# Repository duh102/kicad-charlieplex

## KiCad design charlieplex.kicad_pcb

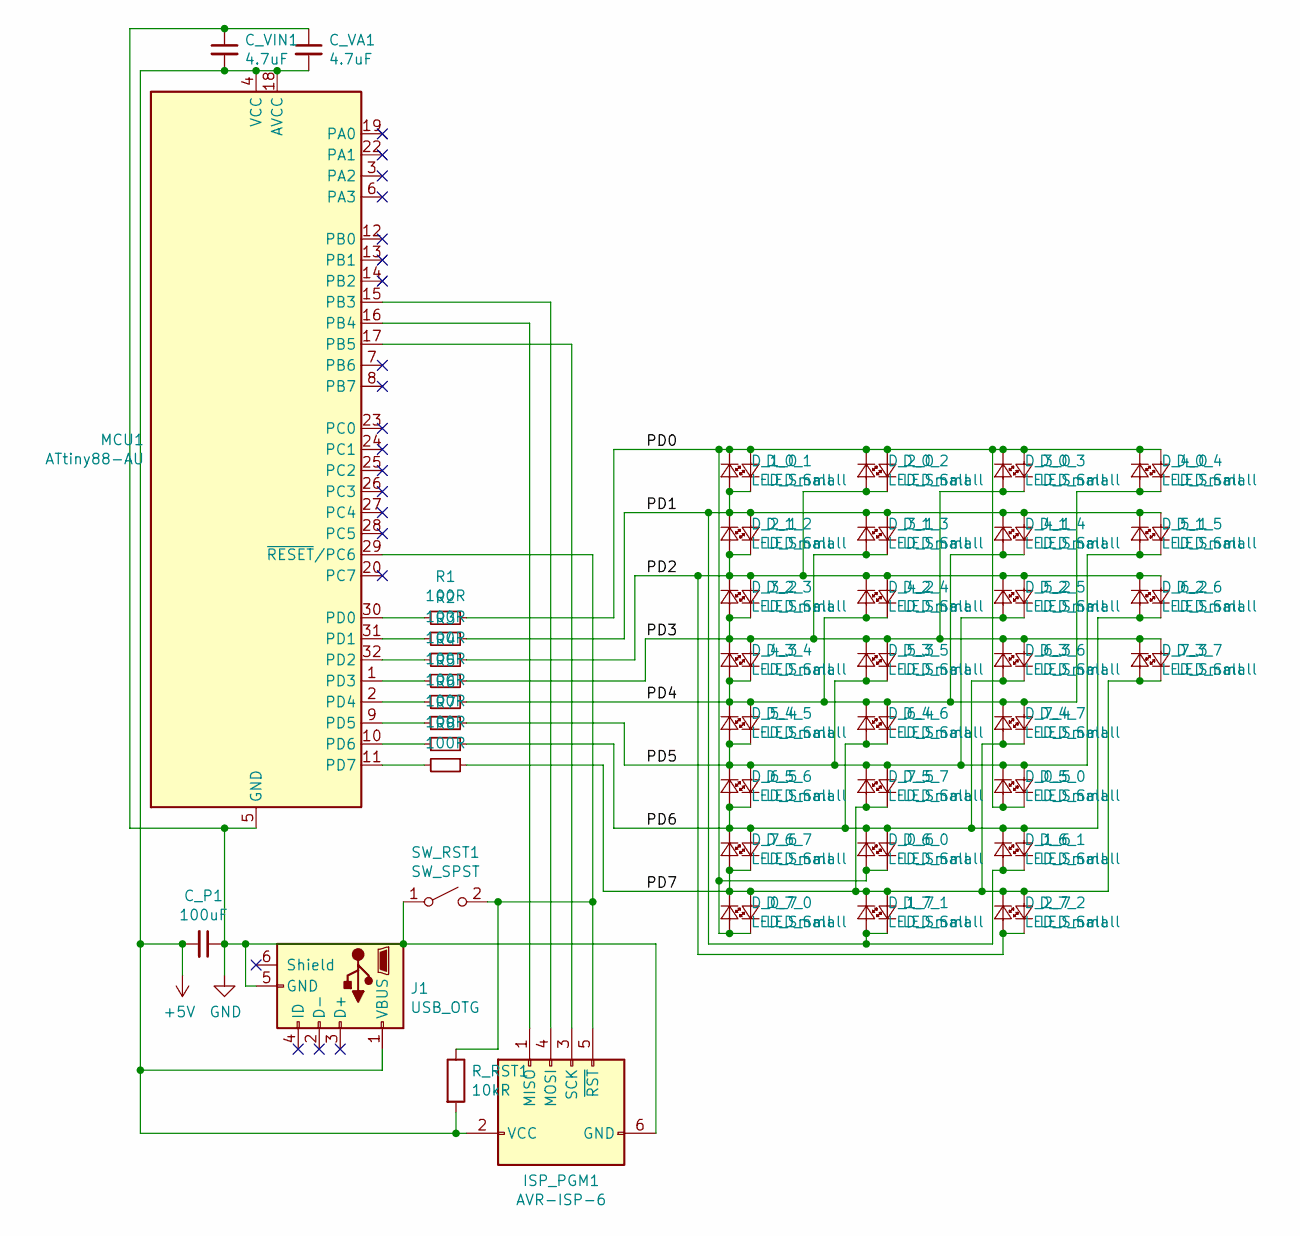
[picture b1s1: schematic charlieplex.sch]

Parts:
C_P1: 100uF; C_0805_2012Metric
C_VA1: 4.7uF; C_0805_2012Metric
C_VIN1: 4.7uF; C_0805_2012Metric
D_0_1, D_0_2, D_0_3, D_0_4, D_0_5, D_0_6, D_0_7, D_1_0, D_1_2, D_1_3, D_1_4, D_1_5, D_1_6, D_1_7, D_2_0, D_2_1, D_2_3, D_2_4, D_2_5, D_2_6, D_2_7, D_3_0, D_3_1, D_3_2, D_3_4, D_3_5, D_3_6, D_3_7, D_4_0, D_4_1, D_4_2, D_4_3, D_4_5, D_4_6, D_4_7, D_5_0, D_5_1, D_5_2, D_5_3, D_5_4, D_5_6, D_5_7, D_6_0, D_6_1, D_6_2, D_6_3, D_6_4, D_6_5, D_6_7, D_7_0, D_7_1, D_7_2, D_7_3, D_7_4, D_7_5, D_7_6: LED_Small; LED_0805_2012Metric
ISP_PGM1: AVR-ISP-6; PinHeader_2x03_P2.54mm_Vertical_SMD
J1: USB_OTG; PinHeader_1x05_P2.54mm_Vertical
MCU1: ATtiny88-AU; TQFP-32_7x7mm_P0.8mm
R1, R2, R3, R4, R5, R6, R7, R8: 100R; R_0805_2012Metric
R_RST1: 10kR; R_0805_2012Metric
SW_RST1: SW_SPST; SW_SPST_CK_RS282G05A3

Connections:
+5V: C_P1.2, C_VA1.2, C_VIN1.2, ISP_PGM1.2 (VCC), J1.1 (VBUS), MCU1.4 (VCC), MCU1.18 (AVCC), R_RST1.2
/PD0: D_0_1.2 (A), D_0_2.2 (A), D_0_3.2 (A), D_0_4.2 (A), D_0_5.2 (A), D_0_6.2 (A), D_0_7.2 (A), D_1_0.1 (K), D_2_0.1 (K), D_3_0.1 (K), D_4_0.1 (K), D_5_0.1 (K), D_6_0.1 (K), D_7_0.1 (K), R1.1
/PD1: D_0_1.1 (K), D_1_0.2 (A), D_1_2.2 (A), D_1_3.2 (A), D_1_4.2 (A), D_1_5.2 (A), D_1_6.2 (A), D_1_7.2 (A), D_2_1.1 (K), D_3_1.1 (K), D_4_1.1 (K), D_5_1.1 (K), D_6_1.1 (K), D_7_1.1 (K), R2.1
/PD2: D_0_2.1 (K), D_1_2.1 (K), D_2_0.2 (A), D_2_1.2 (A), D_2_3.2 (A), D_2_4.2 (A), D_2_5.2 (A), D_2_6.2 (A), D_2_7.2 (A), D_3_2.1 (K), D_4_2.1 (K), D_5_2.1 (K), D_6_2.1 (K), D_7_2.1 (K), R3.1
/PD3: D_0_3.1 (K), D_1_3.1 (K), D_2_3.1 (K), D_3_0.2 (A), D_3_1.2 (A), D_3_2.2 (A), D_3_4.2 (A), D_3_5.2 (A), D_3_6.2 (A), D_3_7.2 (A), D_4_3.1 (K), D_5_3.1 (K), D_6_3.1 (K), D_7_3.1 (K), R4.1
/PD4: D_0_4.1 (K), D_1_4.1 (K), D_2_4.1 (K), D_3_4.1 (K), D_4_0.2 (A), D_4_1.2 (A), D_4_2.2 (A), D_4_3.2 (A), D_4_5.2 (A), D_4_6.2 (A), D_4_7.2 (A), D_5_4.1 (K), D_6_4.1 (K), D_7_4.1 (K), R5.1
/PD5: D_0_5.1 (K), D_1_5.1 (K), D_2_5.1 (K), D_3_5.1 (K), D_4_5.1 (K), D_5_0.2 (A), D_5_1.2 (A), D_5_2.2 (A), D_5_3.2 (A), D_5_4.2 (A), D_5_6.2 (A), D_5_7.2 (A), D_6_5.1 (K), D_7_5.1 (K), R6.1
/PD6: D_0_6.1 (K), D_1_6.1 (K), D_2_6.1 (K), D_3_6.1 (K), D_4_6.1 (K), D_5_6.1 (K), D_6_0.2 (A), D_6_1.2 (A), D_6_2.2 (A), D_6_3.2 (A), D_6_4.2 (A), D_6_5.2 (A), D_6_7.2 (A), D_7_6.1 (K), R7.1
/PD7: D_0_7.1 (K), D_1_7.1 (K), D_2_7.1 (K), D_3_7.1 (K), D_4_7.1 (K), D_5_7.1 (K), D_6_7.1 (K), D_7_0.2 (A), D_7_1.2 (A), D_7_2.2 (A), D_7_3.2 (A), D_7_4.2 (A), D_7_5.2 (A), D_7_6.2 (A), R8.1
GND: C_P1.1, C_VA1.1, C_VIN1.1, ISP_PGM1.6 (GND), J1.5 (GND), MCU1.5 (GND), MCU1.21 (GND), SW_RST1.1 (A)
unnamed: ISP_PGM1.1 (MISO), MCU1.16 (PB4)
unnamed: ISP_PGM1.3 (SCK), MCU1.17 (PB5)
unnamed: ISP_PGM1.4 (MOSI), MCU1.15 (PB3)
unnamed: ISP_PGM1.5 (~RST), MCU1.29 (~RESET~/PC6), R_RST1.1, SW_RST1.2 (B)
unnamed: MCU1.1 (PD3), R4.2
unnamed: MCU1.2 (PD4), R5.2
unnamed: MCU1.9 (PD5), R6.2
unnamed: MCU1.10 (PD6), R7.2
unnamed: MCU1.11 (PD7), R8.2
unnamed: MCU1.30 (PD0), R1.2
unnamed: MCU1.31 (PD1), R2.2
unnamed: MCU1.32 (PD2), R3.2

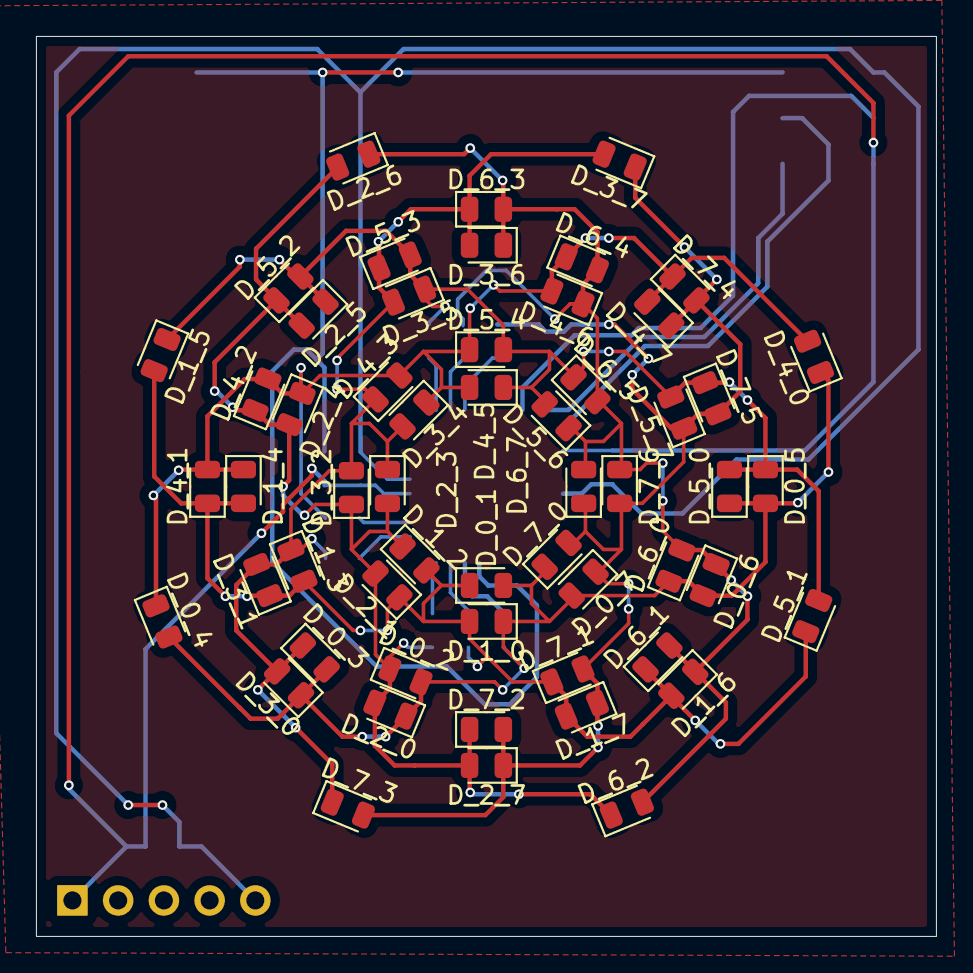
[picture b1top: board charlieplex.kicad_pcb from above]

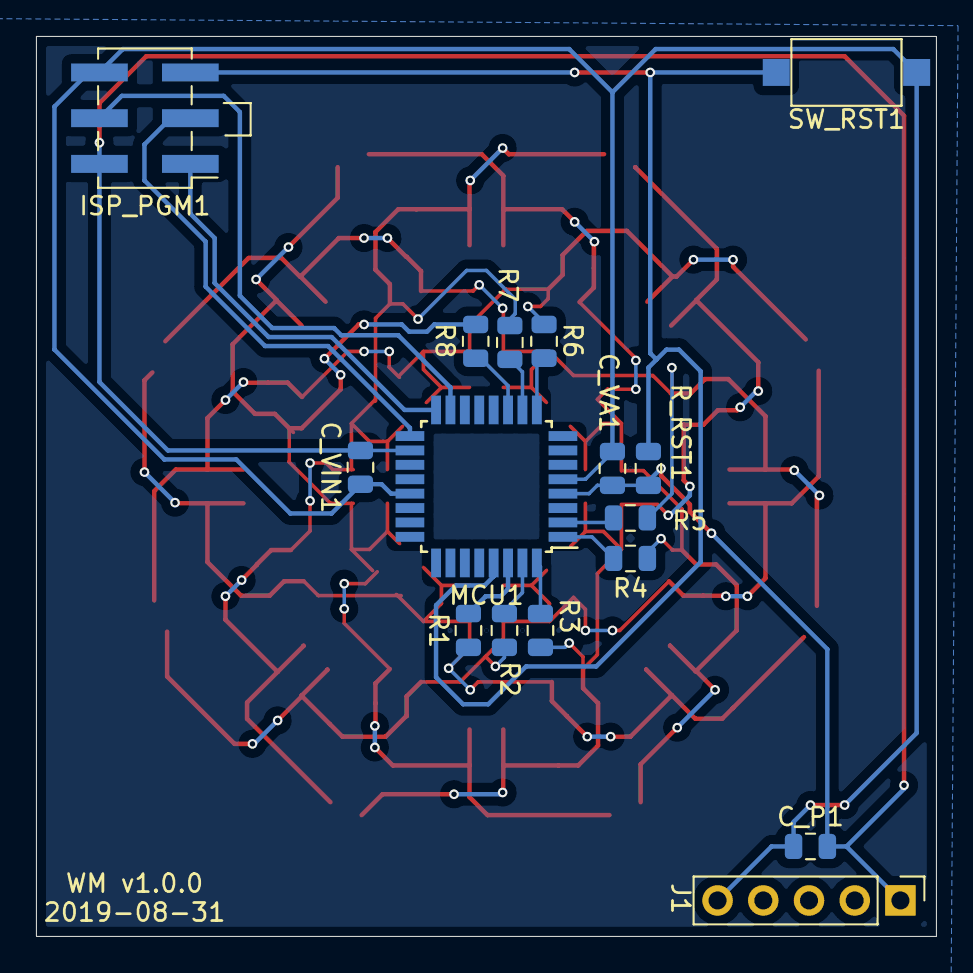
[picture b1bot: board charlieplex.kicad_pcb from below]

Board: 2 copper layers, 50.0 x 50.0 mm, 72 parts (16 on the bottom side), 22 nets.
